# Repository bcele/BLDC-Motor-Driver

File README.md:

# BLDC Motor Driver
Closed-loop BLDC motor driver with PID speed control, ADC-DMA current sensing and 6-step commutation.

## Features
- PID-based speed control
- 6-step commutation
- Dynamic braking and safe-stop handling
- Shunt current sensing via ADC + DMA

## Hardware / Software
- STM32 HAL Libraries
- Custom PCB Design with EAGLE

## Notes
Project supported by TÜBİTAK 2209-B.

### Block Diagram

## Hardware

### PCB Layout

### Assembled PCB

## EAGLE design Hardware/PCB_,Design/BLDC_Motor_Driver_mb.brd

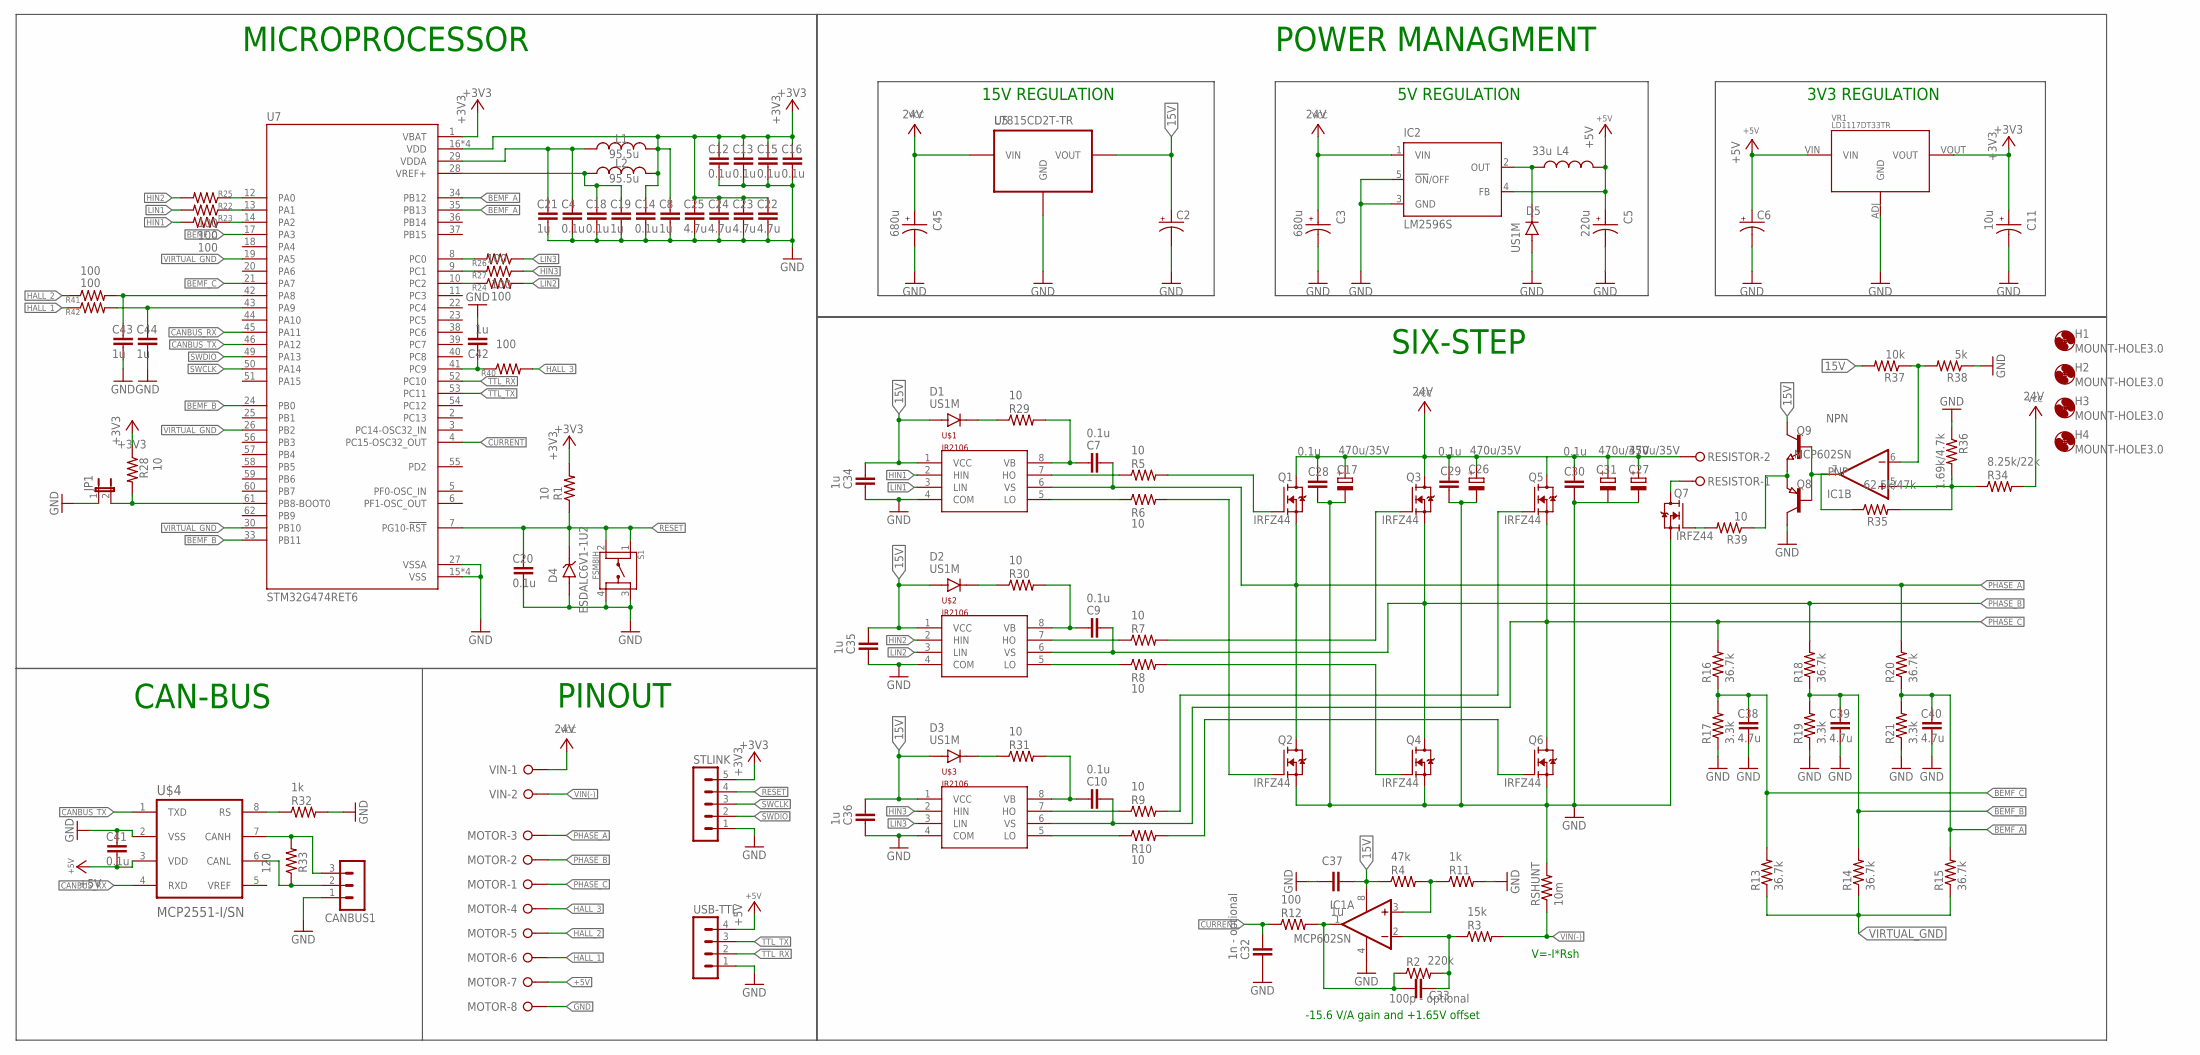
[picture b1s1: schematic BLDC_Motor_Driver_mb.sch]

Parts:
C2, C6: CPOL-US153CLV-0405; 153CLV-0405
C3, C45: 680u; CAP_EEEFK1H221P
C4, C7, C9, C10, C12, C13, C14, C15, C16, C18, C20, C28, C29, C30, C41: 0.1u; C1206
C5: 220u; CAP_EEEFK1H221P
C8, C19, C21, C34, C35, C36, C37, C42, C43, C44: 1u; C1206
C11: 10u; CAP_EEEFK1H221P
C17, C26, C27, C31: 470u/35V; E7,5-16
C22, C23, C24, C25, C38, C39, C40: 4.7u; C1206
C32: 1n - optional; C1206
C33: 100p - optional; C1206
CANBUS1: MA03-1
D1, D2, D3, D5: US1M; DIOM4325X250N
D4: ESDALC6V1-1U2; DIODE_ESDALC6V1-1U2
H1, H2, H3, H4: MOUNT-HOLE3.0; 3,0
IC1: MCP602SN; SO08
IC2: LM2596S; TO263-5
JP1: JP1E; JP1
L1, L2: 95.5u; L3225P
L4: 33u; IHLP4040
MOTOR: W237-08P; W237-8P
Q1, Q2, Q3, Q4, Q5, Q6, Q7: IRFZ44; DPAK254P1524X483-3N
Q8: PNP; SOT23
Q9: NPN; SOT23
R1, R5, R6, R7, R8, R9, R10, R28, R29, R30, R31, R39: 10; R1206
R2: 220k; R1206
R3: 15k; R1206
R4: 47k; R1206
R11, R32: 1k; R1206
R12, R22, R23, R24, R25, R26, R27, R40, R41, R42: 100; R1206
R13, R14, R15, R16, R18, R20: 36.7k; R1206
R17, R19, R21: 3.3k; R1206
R33: 120; R1206
R34: 8.25k/22k; R1206
R35: 62.5k/47k; R1206
R36: 1.69k/4.7k; R1206
R37: 10k; R1206
R38: 5k; R1206
RESISTOR: W237-02P; W237-132
RSHUNT: 10m; R1210
S1: FSM8JH; SW_FSM8JH
STLINK: MA05-1
U5: L7815CD2T-TR; D2PAK
U7: STM32G474RET6; QFP50P1200X1200X160-64N
U$1, U$2, U$3: IR2106; SOIC-8
U$4: MCP2551-I/SN; SOIC127P599X175-8N
USB-TTL: MA04-1
VIN: W237-02P; W237-132
VR1: LD1117DT33TR; DPAK456P1010X240-3N

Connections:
15V: C2.+, C34.2, C35.2, C36.2, C37.1, D1.A, D2.A, D3.A, IC1.8 (V+), Q9.3 (C), R4.1, R37.2, U5.VOUT, U$1.1 (VCC), U$2.1 (VCC), U$3.1 (VCC)
+3V3: C8.1, C11.1, C12.1, C13.1, C14.1, C15.1, C16.1, C22.1, C23.1, C24.1, C25.1, L1.2, L2.2, R1.2, R28.1, STLINK.5, U7.1 (VBAT), U7.16 (VDD), U7.32 (VDD), U7.48 (VDD), U7.64 (VDD), VR1.VOUT
+5V: C5.1, C6.+, C41.2, IC2.4 (FB), L4.2, MOTOR.7, U$4.3 (VDD), USB-TTL.4, VR1.VIN
BEMF_A: C40.1, R15.2, R20.1, R21.2, U7.34 (PB12), U7.35 (PB13)
BEMF_B: C39.1, R14.2, R18.1, R19.2, U7.24 (PB0), U7.33 (PB11)
BEMF_C: C38.1, R13.2, R16.1, R17.2, U7.17 (PA3), U7.21 (PA7)
CANBUS_RX: U7.45 (PA11), U$4.4 (RXD)
CANBUS_TX: U7.46 (PA12), U$4.1 (TXD)
CURRENT: C32.2, R12.1, U7.4 (PC15-OSC32_OUT)
GND: C2.-, C3.2, C4.2, C5.2, C6.-, C8.2, C11.2, C12.2, C13.2, C14.2, C15.2, C16.2, C17.-, C18.2, C19.2, C20.2, C21.2, C22.2, C23.2, C24.2, C25.2, C26.-, C27.-, C28.2, C29.2, C30.2, C31.-, C32.1, C34.1, C35.1, C36.1, C37.2, C38.2, C39.2, C40.2, C41.1, C42.2, C43.2, C44.2, C45.2, CANBUS1.1, D4.2 (A), D5.A, IC1.4 (V-), IC2.3 (GND), IC2.5 (!ON!/OFF), JP1.1, MOTOR.8, Q2.3 (S), Q4.3 (S), Q6.3 (S), Q7.3 (S), Q8.3 (C), R11.2, R17.1, R19.1, R21.1, R32.2, R36.1, R38.1, RSHUNT.2, S1.3, S1.4, STLINK.1, U5.GND, U7.15 (VSS), U7.27 (VSSA), U7.31 (VSS), U7.47 (VSS), U7.63 (VSS), U$1.4 (COM), U$2.4 (COM), U$3.4 (COM), U$4.2 (VSS), USB-TTL.1, VR1.ADJ (GND)
HALL_1: MOTOR.6, R42.1
HALL_2: MOTOR.5, R41.1
HALL_3: MOTOR.4, R40.2
HIN1: R23.2, U$1.2 (HIN)
HIN2: R25.2, U$2.2 (HIN)
HIN3: R27.1, U$3.2 (HIN)
HS2: Q3.1 (G), R7.2
HS3: Q5.1 (G), R9.2
LIN1: R22.2, U$1.3 (LIN)
LIN2: R24.2, U$2.3 (LIN)
LIN3: R26.1, U$3.3 (LIN)
LS1: Q2.1 (G), R6.2
LS2: Q4.1 (G), R8.2
LS3: Q6.1 (G), R10.2
unnamed: Q1.1 (G), R5.2
unnamed: C4.1, C21.1, L1.1, U7.29 (VDDA)
unnamed: R6.1, U$1.5 (LO)
unnamed: C9.1, R30.2, U$2.8 (VB)
unnamed: R5.1, U$1.7 (HO)
unnamed: R26.2, U7.8 (PC0)
unnamed: D1.C (K), R29.1
unnamed: C7.1, R29.2, U$1.8 (VB)
unnamed: R27.2, U7.9 (PC1)
unnamed: R7.1, U$2.7 (HO)
unnamed: R8.1, U$2.5 (LO)
unnamed: JP1.2, R28.2, U7.61 (PB8-BOOT0)
unnamed: C33.1, IC1.2 (-IN), R2.2, R3.1
unnamed: IC1.3 (+IN), R4.2, R11.1
unnamed: C10.1, R31.2, U$3.8 (VB)
unnamed: IC1.7 (OUT), Q8.1 (B), Q9.1 (B), R35.1
unnamed: R9.1, U$3.7 (HO)
unnamed: R10.1, U$3.5 (LO)
unnamed: D2.C (K), R30.1
unnamed: C18.1, C19.1, L2.1, U7.28 (VREF+)
unnamed: C33.2, IC1.1 (OUT), R2.1, R12.2
unnamed: D5.C (K), IC2.2 (OUT), L4.1
unnamed: R22.1, U7.13 (PA1)
unnamed: R23.1, U7.14 (PA2)
unnamed: R24.1, U7.10 (PC2)
unnamed: R25.1, U7.12 (PA0)
unnamed: D3.C (K), R31.1
unnamed: R32.1, U$4.8 (RS)
unnamed: IC1.5 (+IN), R34.1, R35.2, R36.2
unnamed: CANBUS1.3, R33.2, U$4.7 (CANH)
unnamed: Q7.2 (D), RESISTOR.1
unnamed: CANBUS1.2, R33.1, U$4.6 (CANL)
unnamed: IC1.6 (-IN), R37.1, R38.2
unnamed: Q8.2 (E), Q9.2 (E), R39.1
unnamed: Q7.1 (G), R39.2
unnamed: C42.1, R40.1, U7.41 (PC9)
unnamed: C43.1, R41.2, U7.42 (PA8)
unnamed: C44.1, R42.2, U7.43 (PA9)
PHASE_A: C7.2, MOTOR.3, Q1.3 (S), Q2.2 (D), R20.2, U$1.6 (VS)
PHASE_B: C9.2, MOTOR.2, Q3.3 (S), Q4.2 (D), R18.2, U$2.6 (VS)
PHASE_C: C10.2, MOTOR.1, Q5.3 (S), Q6.2 (D), R16.2, U$3.6 (VS)
RESET: C20.1, D4.1 (K), R1.1, S1.1, S1.2, STLINK.4, U7.7 (PG10-!RST)
SWCLK: STLINK.3, U7.50 (PA14)
SWDIO: STLINK.2, U7.49 (PA13)
TTL_RX: U7.52 (PC10), USB-TTL.2
TTL_TX: U7.53 (PC11), USB-TTL.3
VCC: C3.1, C17.+, C26.+, C27.+, C28.1, C29.1, C30.1, C31.+, C45.1, IC2.1 (VIN), Q1.2 (D), Q3.2 (D), Q5.2 (D), R34.2, RESISTOR.2, U5.VIN, VIN.1
VIN(-): R3.2, RSHUNT.1, VIN.2
VIRTUAL_GND: R13.1, R14.1, R15.1, U7.19 (PA5), U7.26 (PB2), U7.30 (PB10)

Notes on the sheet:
MICROPROCESSOR
SIX-STEP
POWER MANAGMENT
15V REGULATION
5V REGULATION
3V3 REGULATION
PINOUT
-15.6 V/A gain and +1.65V offset
V=-I*Rsh
CAN-BUS

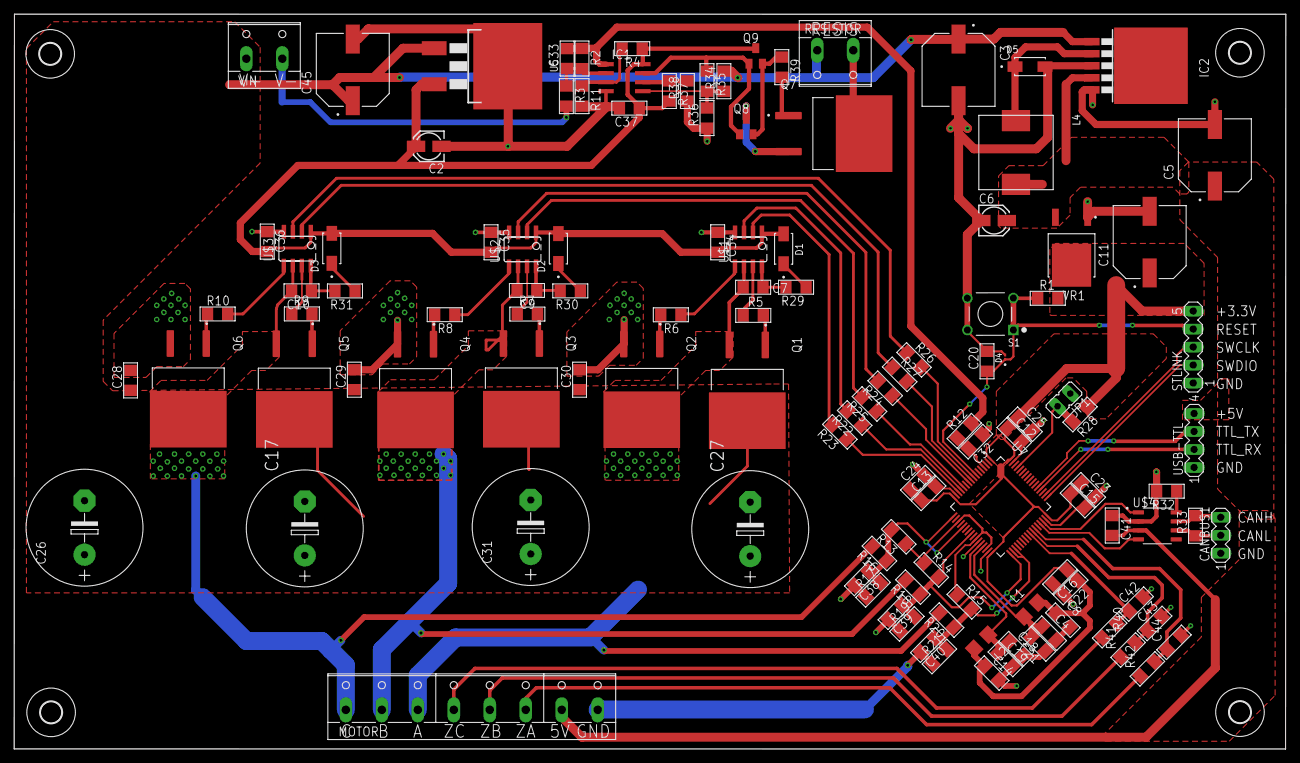
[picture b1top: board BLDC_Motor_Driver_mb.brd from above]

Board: 2 copper layers, 179.6 x 103.8 mm, 125 parts (1 on the bottom side), 73 nets.

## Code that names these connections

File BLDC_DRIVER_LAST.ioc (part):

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Mcu.Name=STM32G474R(B-C-E)Tx
Mcu.Package=LQFP64
Mcu.UserName=STM32G474RETx
PA0.Signal=S_TIM2_CH1
PA1.GPIOParameters=GPIO_Label
PA1.GPIO_Label=LIN_1
PA1.Signal=GPIO_Output
PA10.GPIOParameters=GPIO_Label,GPIO_ModeDefaultEXTI
PA10.GPIO_Label=HALLA
PA10.GPIO_ModeDefaultEXTI=GPIO_MODE_IT_RISING_FALLING
PA10.Signal=GPXTI10
PA2.Signal=S_TIM2_CH3
PA8.GPIOParameters=GPIO_Label,GPIO_ModeDefaultEXTI
PA8.GPIO_Label=HALLB
PA8.GPIO_ModeDefaultEXTI=GPIO_MODE_IT_RISING_FALLING
PA8.Signal=GPXTI8
PA9.Signal=GPIO_Input
PC0.GPIOParameters=GPIO_Label
PC0.GPIO_Label=LIN_3
PC0.Signal=GPIO_Output
PC1.Signal=S_TIM1_CH2
PC15-OSC32_OUT.Signal=GPIO_Input
PC2.GPIOParameters=GPIO_Label
PC2.GPIO_Label=LIN_2
PC2.Signal=GPIO_Output
PC9.GPIOParameters=GPIO_Label,GPIO_ModeDefaultEXTI
PC9.GPIO_Label=HALLC
PC9.GPIO_ModeDefaultEXTI=GPIO_MODE_IT_RISING_FALLING
PC9.Signal=GPXTI9
PF0-OSC_IN.Mode=IN10-Single-Ended
PF0-OSC_IN.Signal=ADC1_IN10
RCC.HSE_VALUE=8000000
RCC.SYSCLKFreq_VALUE=150000000
RCC.SYSCLKSource=RCC_SYSCLKSOURCE_PLLCLK
board=custom

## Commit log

2025-11-20 Move STM32 firmware into Firmware directory
2025-11-20 Add BLDC motor driver PCB (Eagle schematics & board)
2025-11-20 Create image folder
